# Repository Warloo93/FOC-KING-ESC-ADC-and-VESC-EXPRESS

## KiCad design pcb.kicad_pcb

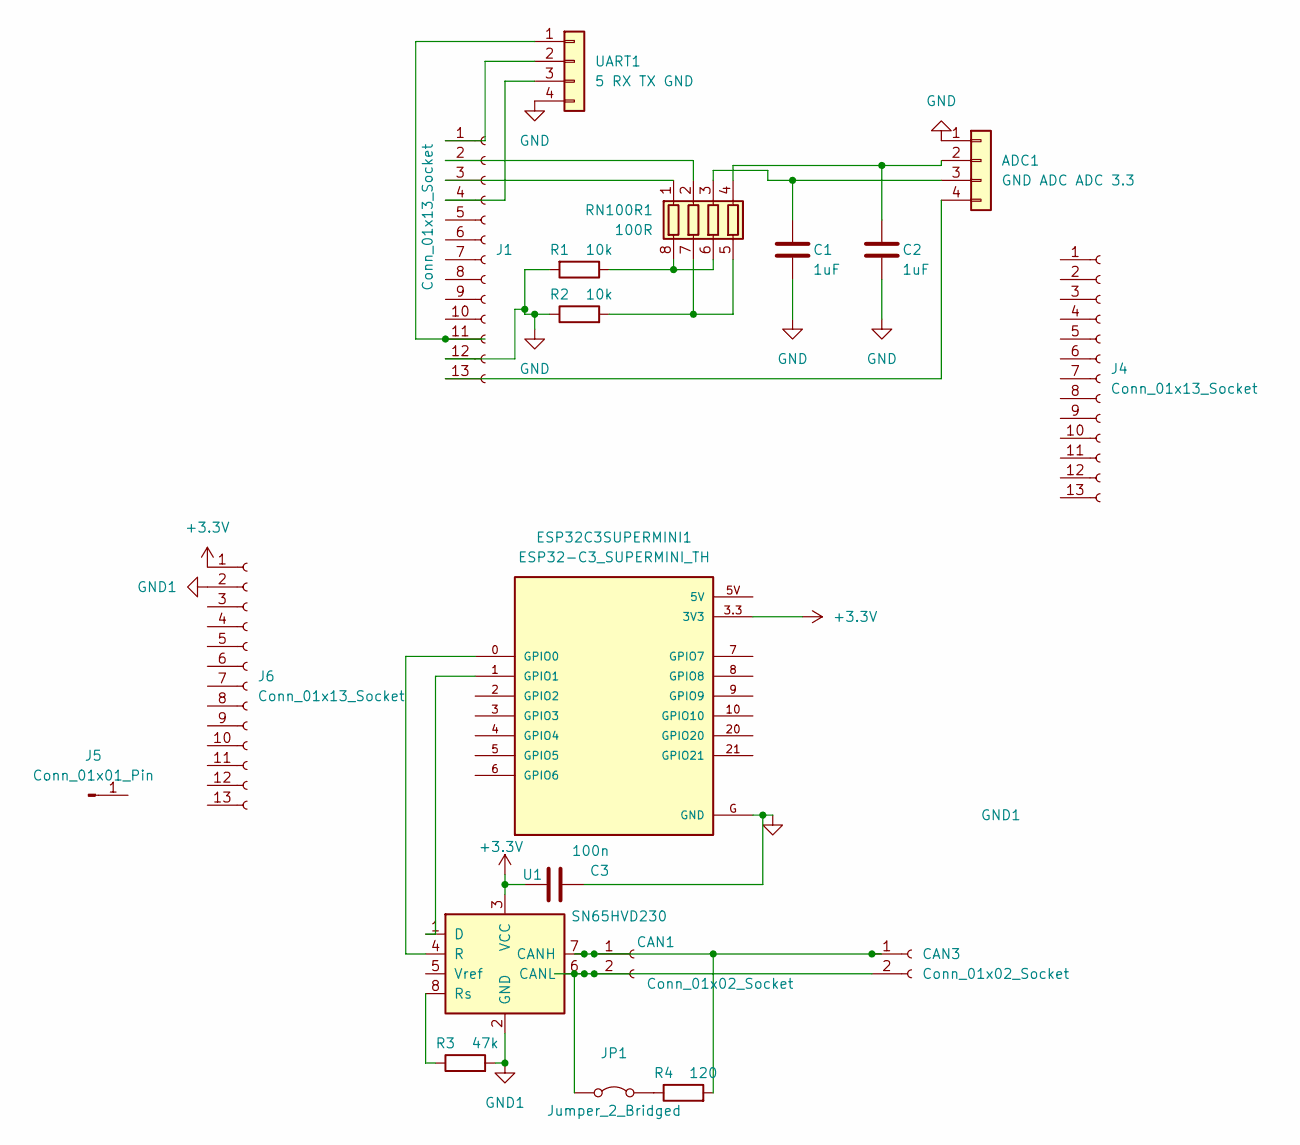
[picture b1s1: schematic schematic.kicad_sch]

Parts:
ADC1: GND ADC ADC 3.3; JST_PH_B4B-PH-K_1x04_P2.00mm_Vertical
C1, C2: 1uF; C_0603_1608Metric; LCSC C15849
C3: 100n; C_0603_1608Metric; LCSC C1591
CAN1, CAN3: Conn_01x02_Socket; JST_PH_B2B-PH-K_1x02_P2.00mm_Vertical
ESP32C3SUPERMINI1: ESP32-C3_SUPERMINI_TH; MODULE_ESP32-C3_SUPERMINI_TH
J1, J4, J6: Conn_01x13_Socket; PinSocket_1x13_P2.54mm_Vertical
J5: Conn_01x01_Pin; PinHeader_1x01_P2.00mm_Vertical
JP1: Jumper_2_Bridged; TestPoint_2Pads_Pitch2.54mm_Drill0.8mm
R1, R2: 10k; R_0603_1608Metric; LCSC C25804
R3: 47k; R_0603_1608Metric; LCSC C25819
R4: 120; R_0603_1608Metric; LCSC C25201
RN100R1: 100R; R_Array_Concave_4x0603; LCSC C25506
U1: SN65HVD230; SOIC-8_3.9x4.9mm_P1.27mm
UART1: 5 RX TX GND; JST_PH_B4B-PH-K_1x04_P2.00mm_Vertical

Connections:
+3.3V: C3.1, ESP32C3SUPERMINI1.3.3 (3V3), J6.1, U1.3 (VCC)
GND: ADC1.1, C1.2, C2.2, J1.12, R1.2, R2.1, UART1.4
GND1: C3.2, ESP32C3SUPERMINI1.G (GND), J6.2, R3.2, U1.2 (GND)
unnamed: ADC1.2, C2.1, RN100R1.4 (R4.1)
unnamed: ADC1.3, C1.1, RN100R1.3 (R3.1)
unnamed: ADC1.4, J1.13
unnamed: CAN1.1, CAN3.1, R4.2, U1.7 (CANH)
unnamed: CAN1.2, CAN3.2, JP1.1 (A), U1.6 (CANL)
unnamed: ESP32C3SUPERMINI1.0 (GPIO0), U1.4 (R)
unnamed: ESP32C3SUPERMINI1.1 (GPIO1), U1.1 (D)
unnamed: J1.1, UART1.2
unnamed: J1.2, RN100R1.2 (R2.1)
unnamed: J1.3, RN100R1.1 (R1.1)
unnamed: J1.4, UART1.3
unnamed: J1.11, UART1.1
unnamed: JP1.2 (B), R4.1
unnamed: R1.1, RN100R1.6 (R3.2), RN100R1.8 (R1.2)
unnamed: R2.2, RN100R1.5 (R4.2), RN100R1.7 (R2.2)
unnamed: R3.1, U1.8 (Rs)

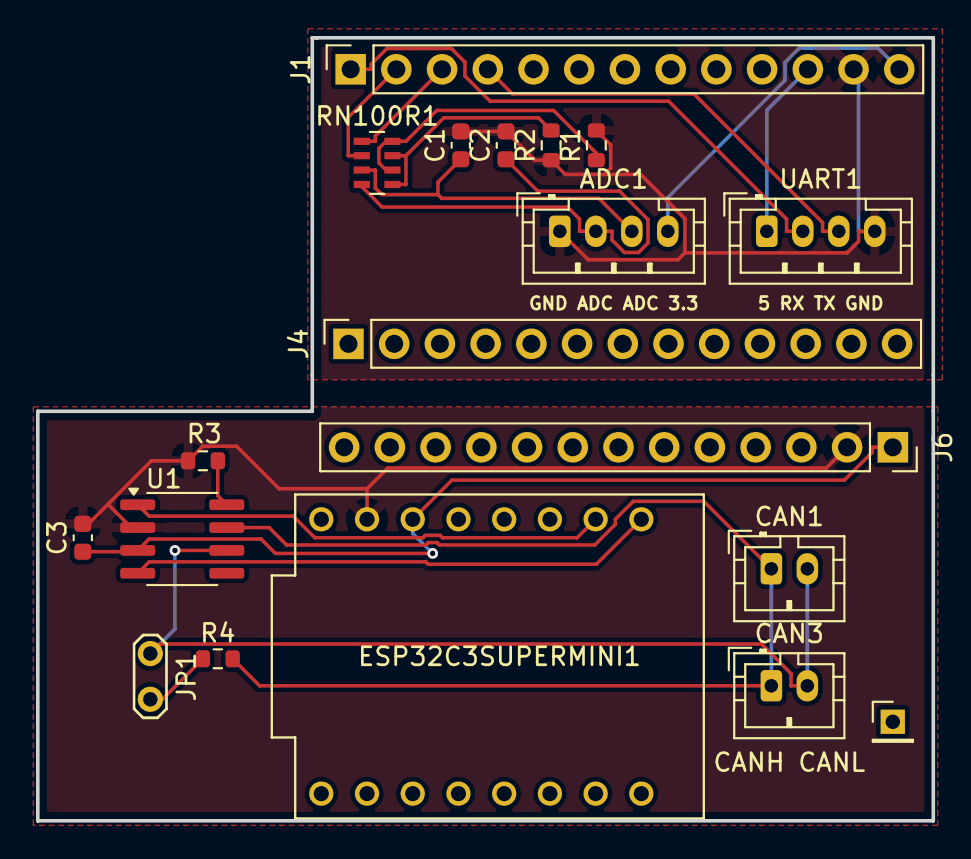
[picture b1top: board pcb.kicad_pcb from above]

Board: 2 copper layers, 49.8 x 43.5 mm, 19 parts (0 on the bottom side), 19 nets.

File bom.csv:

Designator,Footprint,Quantity,Value,LCSC Part #
ADC1,JST_PH_B4B-PH-K_1x04_P2.00mm_Vertical,1,GND ADC ADC 3.3,
"C1, C2",0603,2,1uF,C15849
C3,0603,1,100n,C1591
"CAN1, CAN3",JST_PH_B2B-PH-K_1x02_P2.00mm_Vertical,2,Conn_01x02_Socket,
ESP32C3SUPERMINI1,MODULE_ESP32-C3_SUPERMINI_TH,1,ESP32-C3_SUPERMINI_TH,
"J1, J4, J6",PinSocket_1x13_P2.54mm_Vertical,3,Conn_01x13_Socket,
J5,PinHeader_1x01_P2.00mm_Vertical,1,Conn_01x01_Pin,
JP1,TestPoint_2Pads_Pitch2.54mm_Drill0.8mm,1,Jumper_2_Bridged,
"R1, R2",0603,2,10k,C25804
R3,0603,1,47k,C25819
R4,0603,1,120,C25201
RN100R1,R_Array_Concave_4x0603,1,100R,C25506
U1,SOIC-8_3.9x4.9mm_P1.27mm,1,SN65HVD230,
UART1,JST_PH_B4B-PH-K_1x04_P2.00mm_Vertical,1,5 RX TX GND,

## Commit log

2025-08-07 Rename Snímka obrazovky 2025-08-07 120029.png to schematic
